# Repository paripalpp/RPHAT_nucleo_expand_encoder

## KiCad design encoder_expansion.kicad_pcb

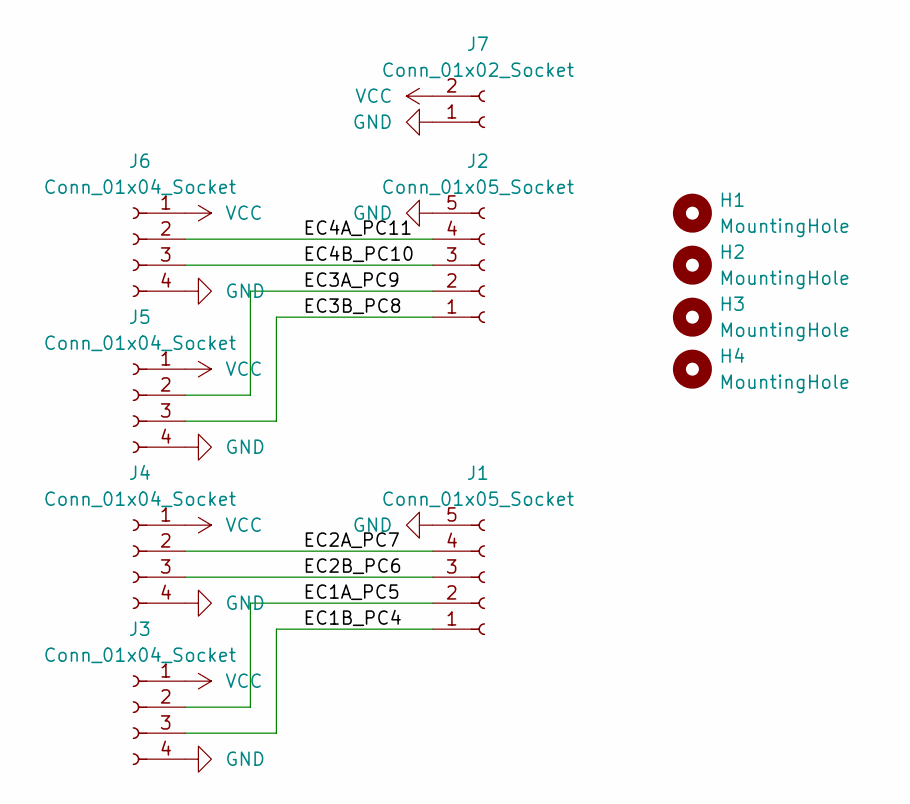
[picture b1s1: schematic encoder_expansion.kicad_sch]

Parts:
H1, H2, H3, H4: MountingHole; MountingHole_3.2mm_M3_Pad_Via
J1, J2: Conn_01x05_Socket; JST_XA_S05B-XASK-1_1x05_P2.50mm_Horizontal
J3, J4, J5, J6: Conn_01x04_Socket; JST_XA_S04B-XASK-1_1x04_P2.50mm_Horizontal
J7: Conn_01x02_Socket; JST_XA_S02B-XASK-1_1x02_P2.50mm_Horizontal

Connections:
/EC1A_PC5: J1.2, J3.2
/EC1B_PC4: J1.1, J3.3
/EC2A_PC7: J1.4, J4.2
/EC2B_PC6: J1.3, J4.3
/EC3A_PC9: J2.2, J5.2
/EC3B_PC8: J2.1, J5.3
/EC4A_PC11: J2.4, J6.2
/EC4B_PC10: J2.3, J6.3
GND: J1.5, J2.5, J3.4, J4.4, J5.4, J6.4, J7.1
VCC: J3.1, J4.1, J5.1, J6.1, J7.2

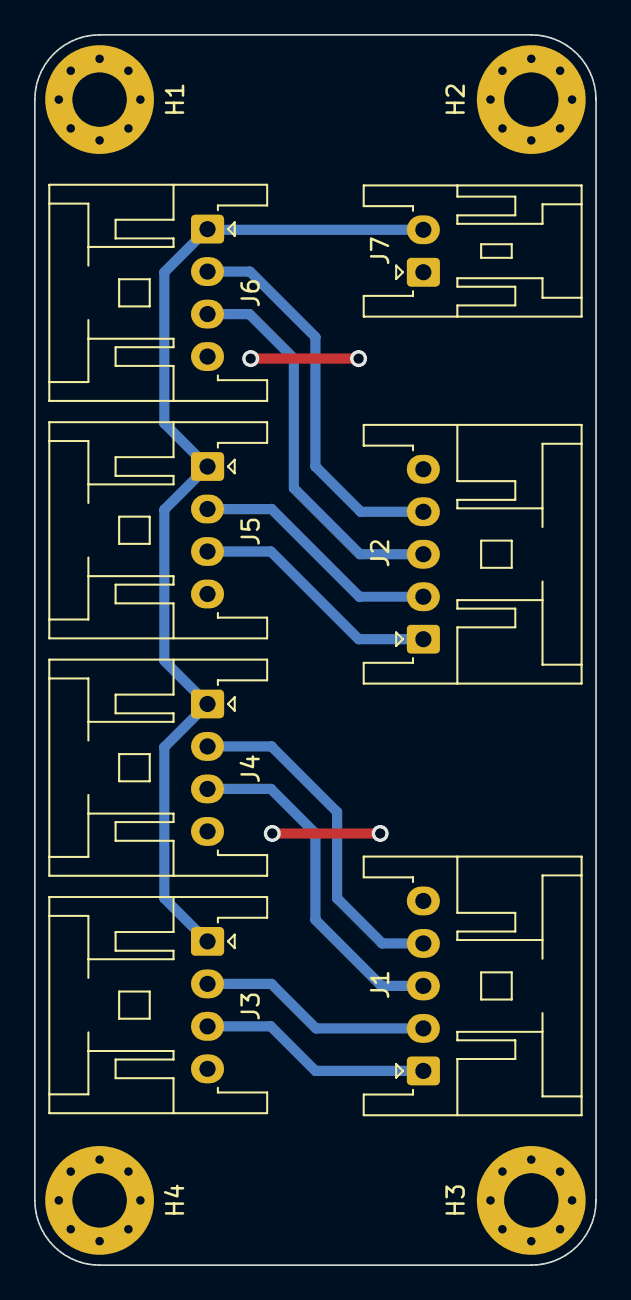
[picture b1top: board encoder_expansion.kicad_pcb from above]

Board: 2 copper layers, 33.0 x 72.4 mm, 11 parts (0 on the bottom side), 10 nets.

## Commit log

2024-06-17 add mounting hole and silk
